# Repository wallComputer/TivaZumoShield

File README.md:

# TivaZumoShield
PCB Design for a TI TM4C123GH6PMI based board for the Pololu Zumo Robot

Most packages were used from http://componentsearchengine.com

If any package is not available there, let me know and I will add.

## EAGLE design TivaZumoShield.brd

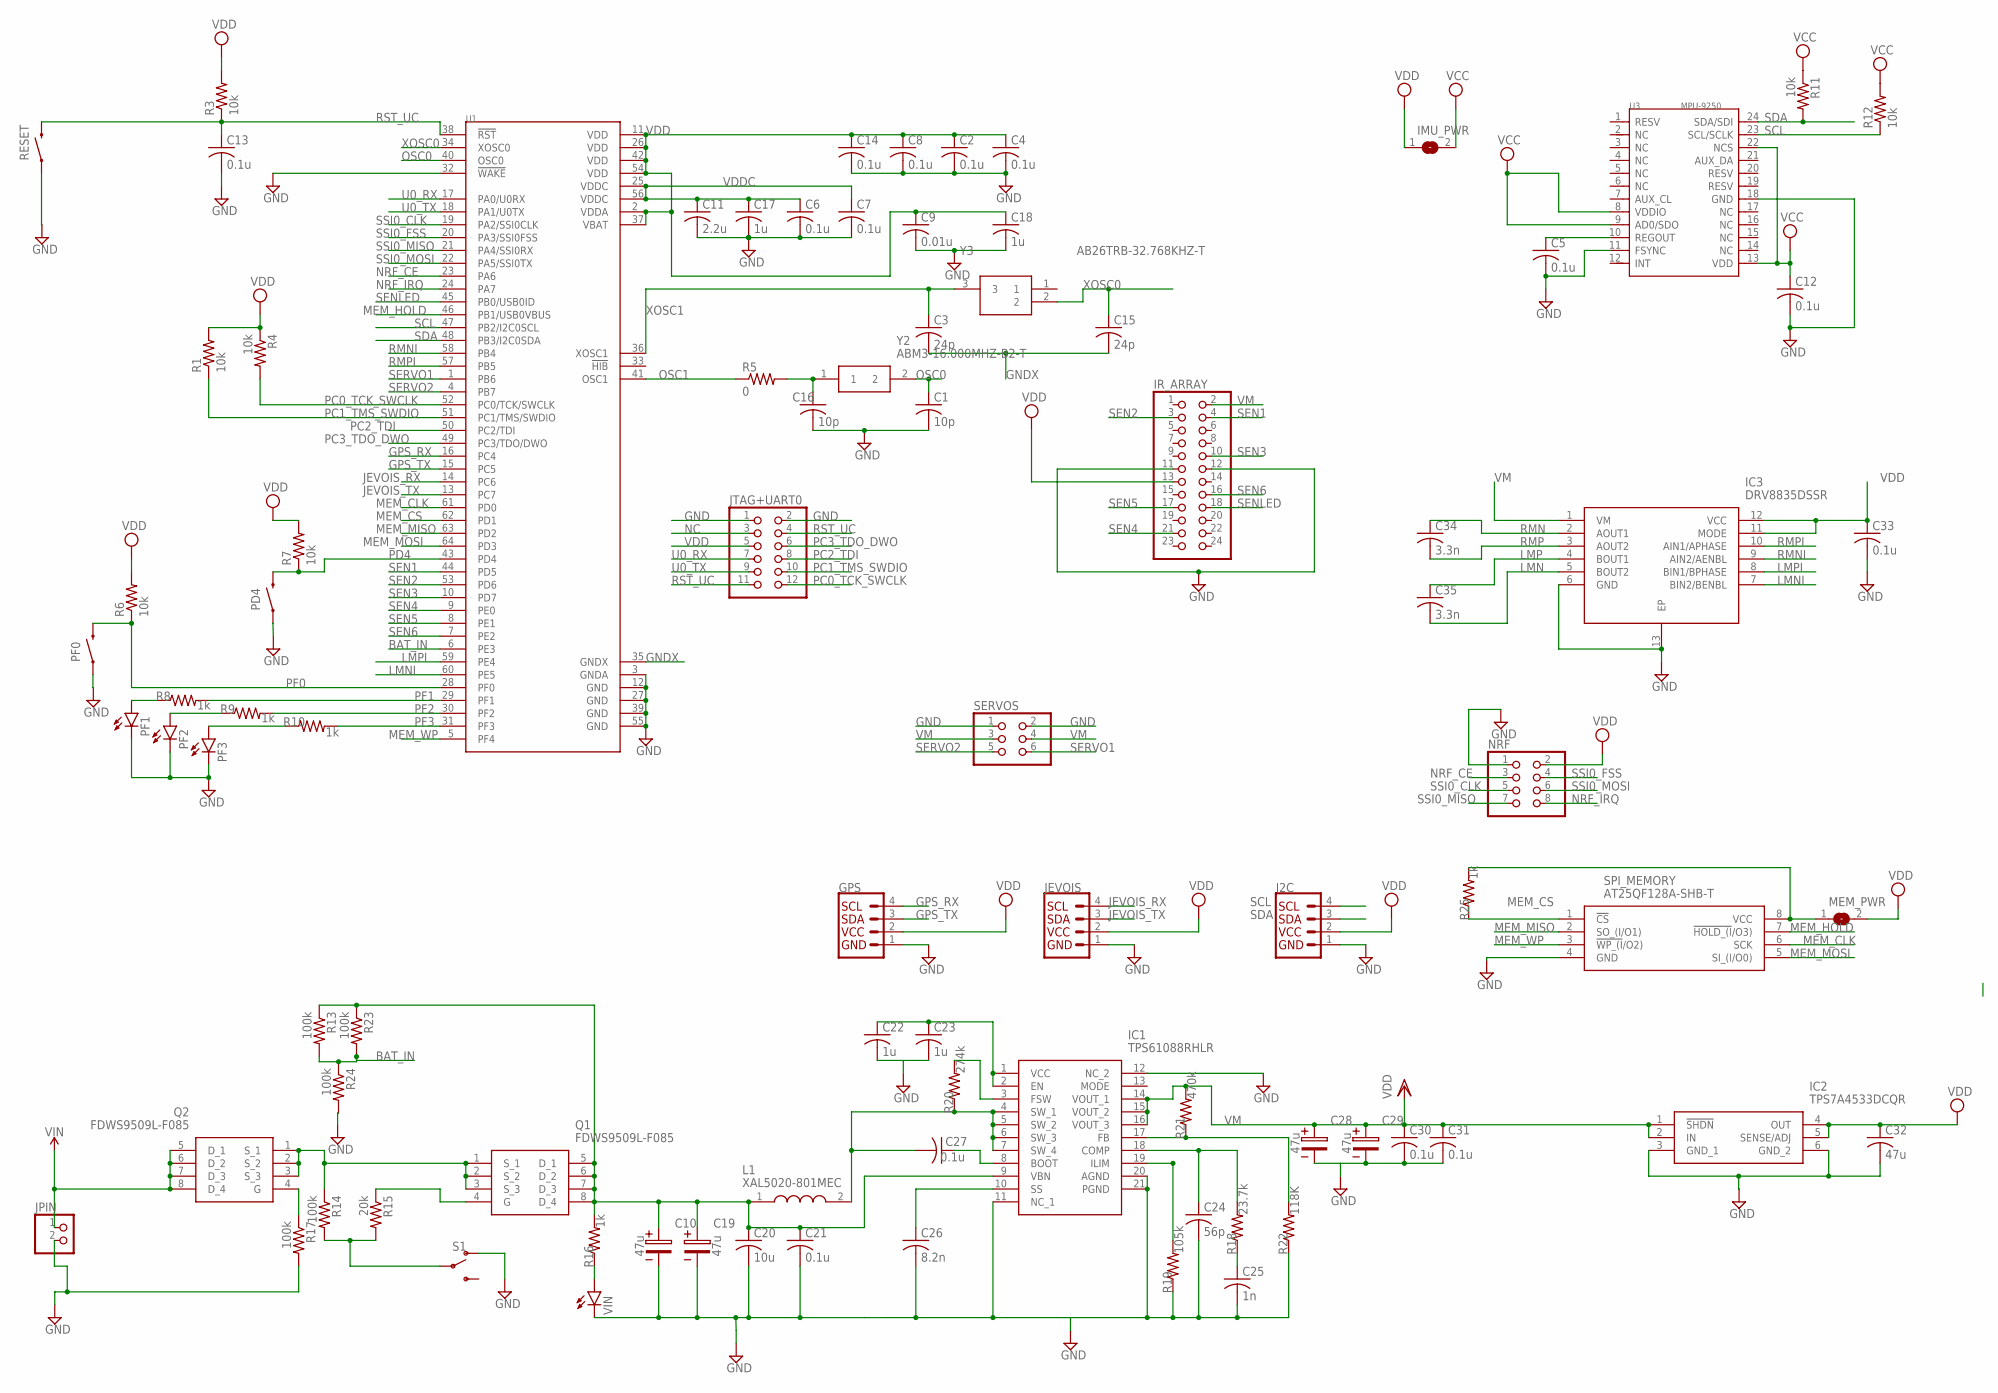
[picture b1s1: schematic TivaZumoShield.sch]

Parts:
C1, C16: 10p; C0603
C2, C4, C5, C6, C7, C8, C12, C13, C14, C21, C27, C30, C31, C33: 0.1u; C0603
C3, C15: 24p; C0603
C9: 0.01u; C0603
C10, C19, C28, C29: 47u; 3X1.6X1.4(BXCXA)
C11: 2.2u; C0603
C17, C18, C22, C23: 1u; C0603
C20: 10u; C0603
C24: 56p; C0603
C25: 1n; C0603
C26: 8.2n; C0603
C32: 47u; C0805K
C34, C35: 3.3n; C0603
GPS: QWIIC_CONNECTORJS-1MM; 1X04_1MM_RA
I2C: QWIIC_CONNECTORJS-1MM; 1X04_1MM_RA
IC1: TPS61088RHLR; RHL(R-PVQFN-N20)_1
IC2: TPS7A4533DCQR; SOT127P706X180-6N
IC3: DRV8835DSSR; SON50P200X300X80-13N
IMU_PWR: SJ
IR_ARRAY: PINHD-2X12; 2X12
JEVOIS: QWIIC_CONNECTORJS-1MM; 1X04_1MM_RA
JPIN: PINHD-1X2; 1X02
JTAG+UART0: PINHD-2X6; 2X06
L1: XAL5020-801MEC; XAL5020801MEC
MEM_PWR: SJ
NRF: PINHD-2X4; 2X04
PD4: RS032G05A3SM-SPST-MOMENTARY-SWSMD-1101NE; TACTILE-SWITCH-1101NE
PF0: RS032G05A3SM-SPST-MOMENTARY-SWSMD-1101NE; TACTILE-SWITCH-1101NE
PF1: LED-RED0603; 0603-RED
PF2: LED-GREEN0603; 0603-GREEN
PF3: LED-BLUE0603; 0603-BLUE
Q1, Q2: FDWS9509L-F085; FDWS9510LF085
R1, R3, R4, R6, R7, R11, R12: 10k; R0603
R5: 0; R0603
R8, R9, R10, R16, R25: 1k; R0603
R13, R14, R17, R23, R24: 100k; R0603
R15: 20k; R0603
R18: 23.7k; R0603
R19: 105k; R0603
R20: 274k; R0603
R21: 470k; R0603
R22: 118K; R0603
RESET: RS032G05A3SM-SPST-MOMENTARY-SWSMD-1101NE; TACTILE-SWITCH-1101NE
S1: SWITCH-SPDT-SMD-RIGHT-ANGLE; SWITCH_SPST_SMD_A
SERVOS: PINHD-2X3; 2X03
SPI_MEMORY: AT25QF128A-SHB-T; SOIC127P790X216-8N
U1: TM4C123GH6PMI; QFP50P1200X1200X160-64N
U3: MPU-9250; QFN24G-0.4-3X3MM
VIN: LED-YELLOW0603; 0603-YELLOW
Y2: ABM3-16.000MHZ-B2-T; ABM-3
Y3: AB26TRB-32.768KHZ-T; AB26TRB

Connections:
BAT_IN: R13.2, R23.2, R24.1, U1.6 (PE3)
GND: C1.2, C2.2, C4.2, C5.2, C6.2, C7.2, C8.2, C9.2, C10.2, C11.2, C12.2, C13.2, C14.2, C16.2, C17.2, C18.2, C19.2, C20.2, C21.2, C22.2, C23.2, C24.2, C25.2, C26.2, C28.2, C29.2, C30.2, C31.2, C32.2, C33.2, GPS.1 (GND), I2C.1 (GND), IC1.11 (NC_1), IC1.12 (NC_2), IC1.20 (AGND), IC1.21 (PGND), IC2.3 (GND_1), IC2.6 (GND_2), IC3.6 (GND), IC3.13 (EP), IR_ARRAY.11, IR_ARRAY.12, JEVOIS.1 (GND), JPIN.2, JTAG+UART0.1, JTAG+UART0.2, NRF.1, PD4.1, PF0.1, PF1.C, PF2.C, PF3.C, R17.2, R19.1, R22.1, R24.2, RESET.1, S1.1 (O), SERVOS.1, SERVOS.2, SPI_MEMORY.4 (GND), U1.3 (GNDA), U1.12 (GND), U1.27 (GND), U1.32 (!WAKE), U1.39 (GND), U1.55 (GND), U3.11 (FSYNC), U3.18 (GND), VIN.C
GNDX: C3.2, C15.2, U1.35 (GNDX)
GPS_RX: GPS.4 (SCL), U1.16 (PC4)
GPS_TX: GPS.3 (SDA), U1.15 (PC5)
JEVOIS_RX: JEVOIS.4 (SCL), U1.14 (PC6)
JEVOIS_TX: JEVOIS.3 (SDA), U1.13 (PC7)
LMN: C35.2, IC3.5 (BOUT2)
LMNI: IC3.7 (BIN2/BENBL), U1.60 (PE5)
LMP: C35.1, IC3.4 (BOUT1)
LMPI: IC3.8 (BIN1/BPHASE), U1.59 (PE4)
MEM_CLK: SPI_MEMORY.6 (SCK), U1.61 (PD0)
MEM_CS: R25.1, SPI_MEMORY.1 (!CS), U1.62 (PD1)
MEM_HOLD: SPI_MEMORY.7 (!HOLD_(I!/O3)), U1.46 (PB1/USB0VBUS)
MEM_MISO: SPI_MEMORY.2 (SO_(I/O1)), U1.63 (PD2)
MEM_MOSI: SPI_MEMORY.5 (SI_(I/O0)), U1.64 (PD3)
MEM_WP: SPI_MEMORY.3 (!WP_(I!/O2)), U1.5 (PF4)
unnamed: PF1.A, R8.1
unnamed: C16.1, R5.2, Y2.1
unnamed: R14.2, R15.2, S1.2
unnamed: C5.1, U3.10 (REGOUT)
unnamed: MEM_PWR.1, R25.2, SPI_MEMORY.8 (VCC)
unnamed: C10.1, C19.1, C20.1, C21.1, IC1.9 (VBN), L1.1, Q1.5 (D_1), Q1.6 (D_2), Q1.7 (D_3), Q1.8 (D_4), R13.1, R16.2, R23.1
unnamed: PF2.A, R9.1
unnamed: PF3.A, R10.1
unnamed: Q1.4 (G), R15.1
unnamed: Q1.1 (S_1), Q1.2 (S_2), Q1.3 (S_3), Q2.1 (S_1), Q2.2 (S_2), Q2.3 (S_3), R14.1
unnamed: R16.1, VIN.A
unnamed: C27.2, IC1.4 (SW_1), IC1.5 (SW_2), IC1.6 (SW_3), IC1.7 (SW_4), L1.2, R20.1
unnamed: Q2.4 (G), R17.1
unnamed: C24.1, IC1.18 (COMP), R18.2
unnamed: C22.1, C23.1, IC1.1 (VCC), IC1.2 (EN)
unnamed: C25.1, R18.1
unnamed: IC1.3 (FSW), R20.2
unnamed: IC1.19 (ILIM), R19.2
unnamed: C26.1, IC1.10 (SS)
unnamed: C27.1, IC1.8 (BOOT)
unnamed: IC1.17 (FB), R21.1, R22.2
NC: JTAG+UART0.3
NRF_CE: NRF.3, U1.23 (PA6)
NRF_IRQ: NRF.8, U1.24 (PA7)
OSC0: C1.1, U1.40 (OSC0), Y2.2
OSC1: R5.1, U1.41 (OSC1)
PC0_TCK_SWCLK: JTAG+UART0.12, R4.2, U1.52 (PC0/TCK/SWCLK)
PC1_TMS_SWDIO: JTAG+UART0.10, R1.1, U1.51 (PC1/TMS/SWDIO)
PC2_TDI: JTAG+UART0.8, U1.50 (PC2/TDI)
PC3_TDO_DWO: JTAG+UART0.6, U1.49 (PC3/TDO/DWO)
PD4: PD4.2, R7.1, U1.43 (PD4)
PF0: PF0.2, R6.1, U1.28 (PF0)
PF1: R8.2, U1.29 (PF1)
PF2: R9.2, U1.30 (PF2)
PF3: R10.2, U1.31 (PF3)
RMN: C34.1, IC3.2 (AOUT1)
RMNI: IC3.9 (AIN2/AENBL), U1.58 (PB4)
RMP: C34.2, IC3.3 (AOUT2)
RMPI: IC3.10 (AIN1/APHASE), U1.57 (PB5)
RST_UC: C13.1, JTAG+UART0.4, JTAG+UART0.11, R3.1, RESET.2, U1.38 (!RST)
SCL: I2C.4 (SCL), R12.1, U1.47 (PB2/I2C0SCL), U3.23 (SCL/SCLK)
SDA: I2C.3 (SDA), R11.2, U1.48 (PB3/I2C0SDA), U3.24 (SDA/SDI)
SEN1: IR_ARRAY.4, U1.44 (PD5)
SEN2: IR_ARRAY.3, U1.53 (PD6)
SEN3: IR_ARRAY.10, U1.10 (PD7)
SEN4: IR_ARRAY.21, U1.9 (PE0)
SEN5: IR_ARRAY.17, U1.8 (PE1)
SEN6: IR_ARRAY.16, U1.7 (PE2)
SENLED: IR_ARRAY.18, U1.45 (PB0/USB0ID)
SERVO1: SERVOS.6, U1.1 (PB6)
SERVO2: SERVOS.5, U1.4 (PB7)
SSI0_CLK: NRF.5, U1.19 (PA2/SSI0CLK)
SSI0_FSS: NRF.4, U1.20 (PA3/SSI0FSS)
SSI0_MISO: NRF.7, U1.21 (PA4/SSI0RX)
SSI0_MOSI: NRF.6, U1.22 (PA5/SSI0TX)
U0_RX: JTAG+UART0.7, U1.17 (PA0/U0RX)
U0_TX: JTAG+UART0.9, U1.18 (PA1/U0TX)
VCC: C12.1, IMU_PWR.2, R11.1, R12.2, U3.8 (VDDIO), U3.9 (AD0/SDO), U3.13 (VDD), U3.22 (NCS)
VDD: C2.1, C4.1, C8.1, C9.1, C14.1, C18.1, C32.1, C33.1, GPS.2 (VCC), I2C.2 (VCC), IC2.4 (OUT), IC2.5 (SENSE/ADJ), IC3.11 (MODE), IC3.12 (VCC), IMU_PWR.1, IR_ARRAY.13, JEVOIS.2 (VCC), JTAG+UART0.5, MEM_PWR.2, NRF.2, R1.2, R3.2, R4.1, R6.2, R7.2, U1.2 (VDDA), U1.11 (VDD), U1.26 (VDD), U1.37 (VBAT), U1.42 (VDD), U1.54 (VDD)
VDDC: C6.1, C7.1, C11.1, C17.1, U1.25 (VDDC), U1.56 (VDDC)
VIN: JPIN.1, Q2.5 (D_1), Q2.6 (D_2), Q2.7 (D_3), Q2.8 (D_4)
VM: C28.1, C29.1, C30.1, C31.1, IC1.14 (VOUT_1), IC1.15 (VOUT_2), IC1.16 (VOUT_3), IC2.1 (!SHDN), IC2.2 (IN), IC3.1 (VM), IR_ARRAY.2, R21.2, SERVOS.3, SERVOS.4
XOSC0: C15.1, U1.34 (XOSC0), Y3.2
XOSC1: C3.1, U1.36 (XOSC1), Y3.3

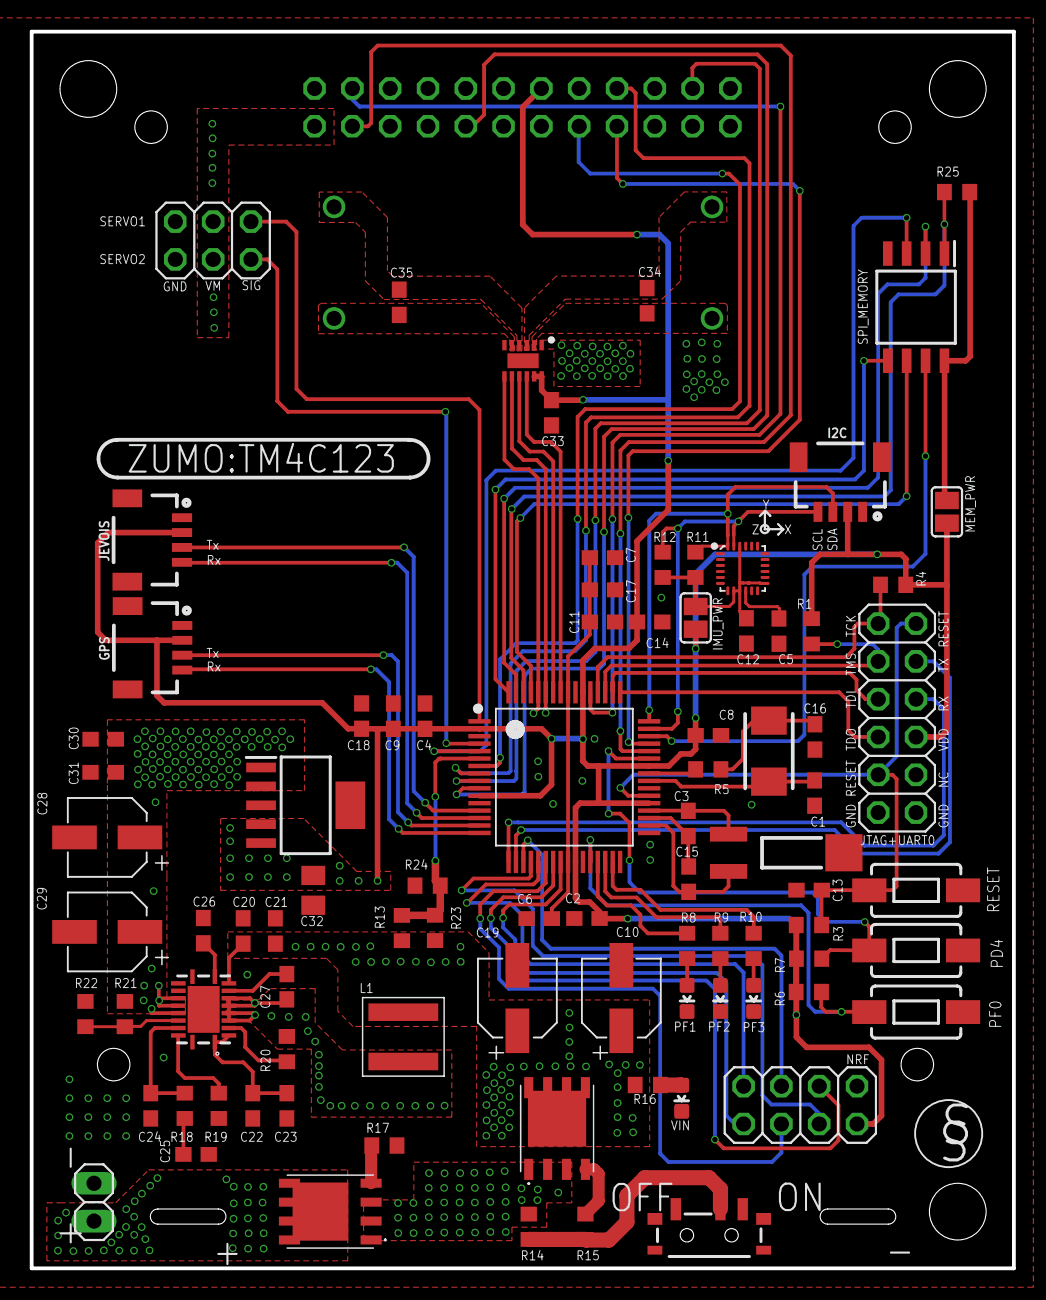
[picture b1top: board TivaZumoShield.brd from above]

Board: 2 copper layers, 66.0 x 83.1 mm, 88 parts (1 on the bottom side), 80 nets.

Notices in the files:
parts and their libraries:
SparkFun-Switches: Licensing: Creative Commons ShareAlike 4.0 International - https://creativecommons.org/licenses/by-sa/4.0
Wurth_Elektronik_Passive_Capacitors_rev1: Copyright: Würth Elektronik
